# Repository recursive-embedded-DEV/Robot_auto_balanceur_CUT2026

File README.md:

# Robot_auto_balanceur_CUT2026
Ce répertoire présente les différentes étapes de conception matérielle et logicielle d'un robot auto-balanceur à deux roues créé dans le cadre d'un projet étudiant en 2026 à l'École de Technologie Supérieure (ÉTS).

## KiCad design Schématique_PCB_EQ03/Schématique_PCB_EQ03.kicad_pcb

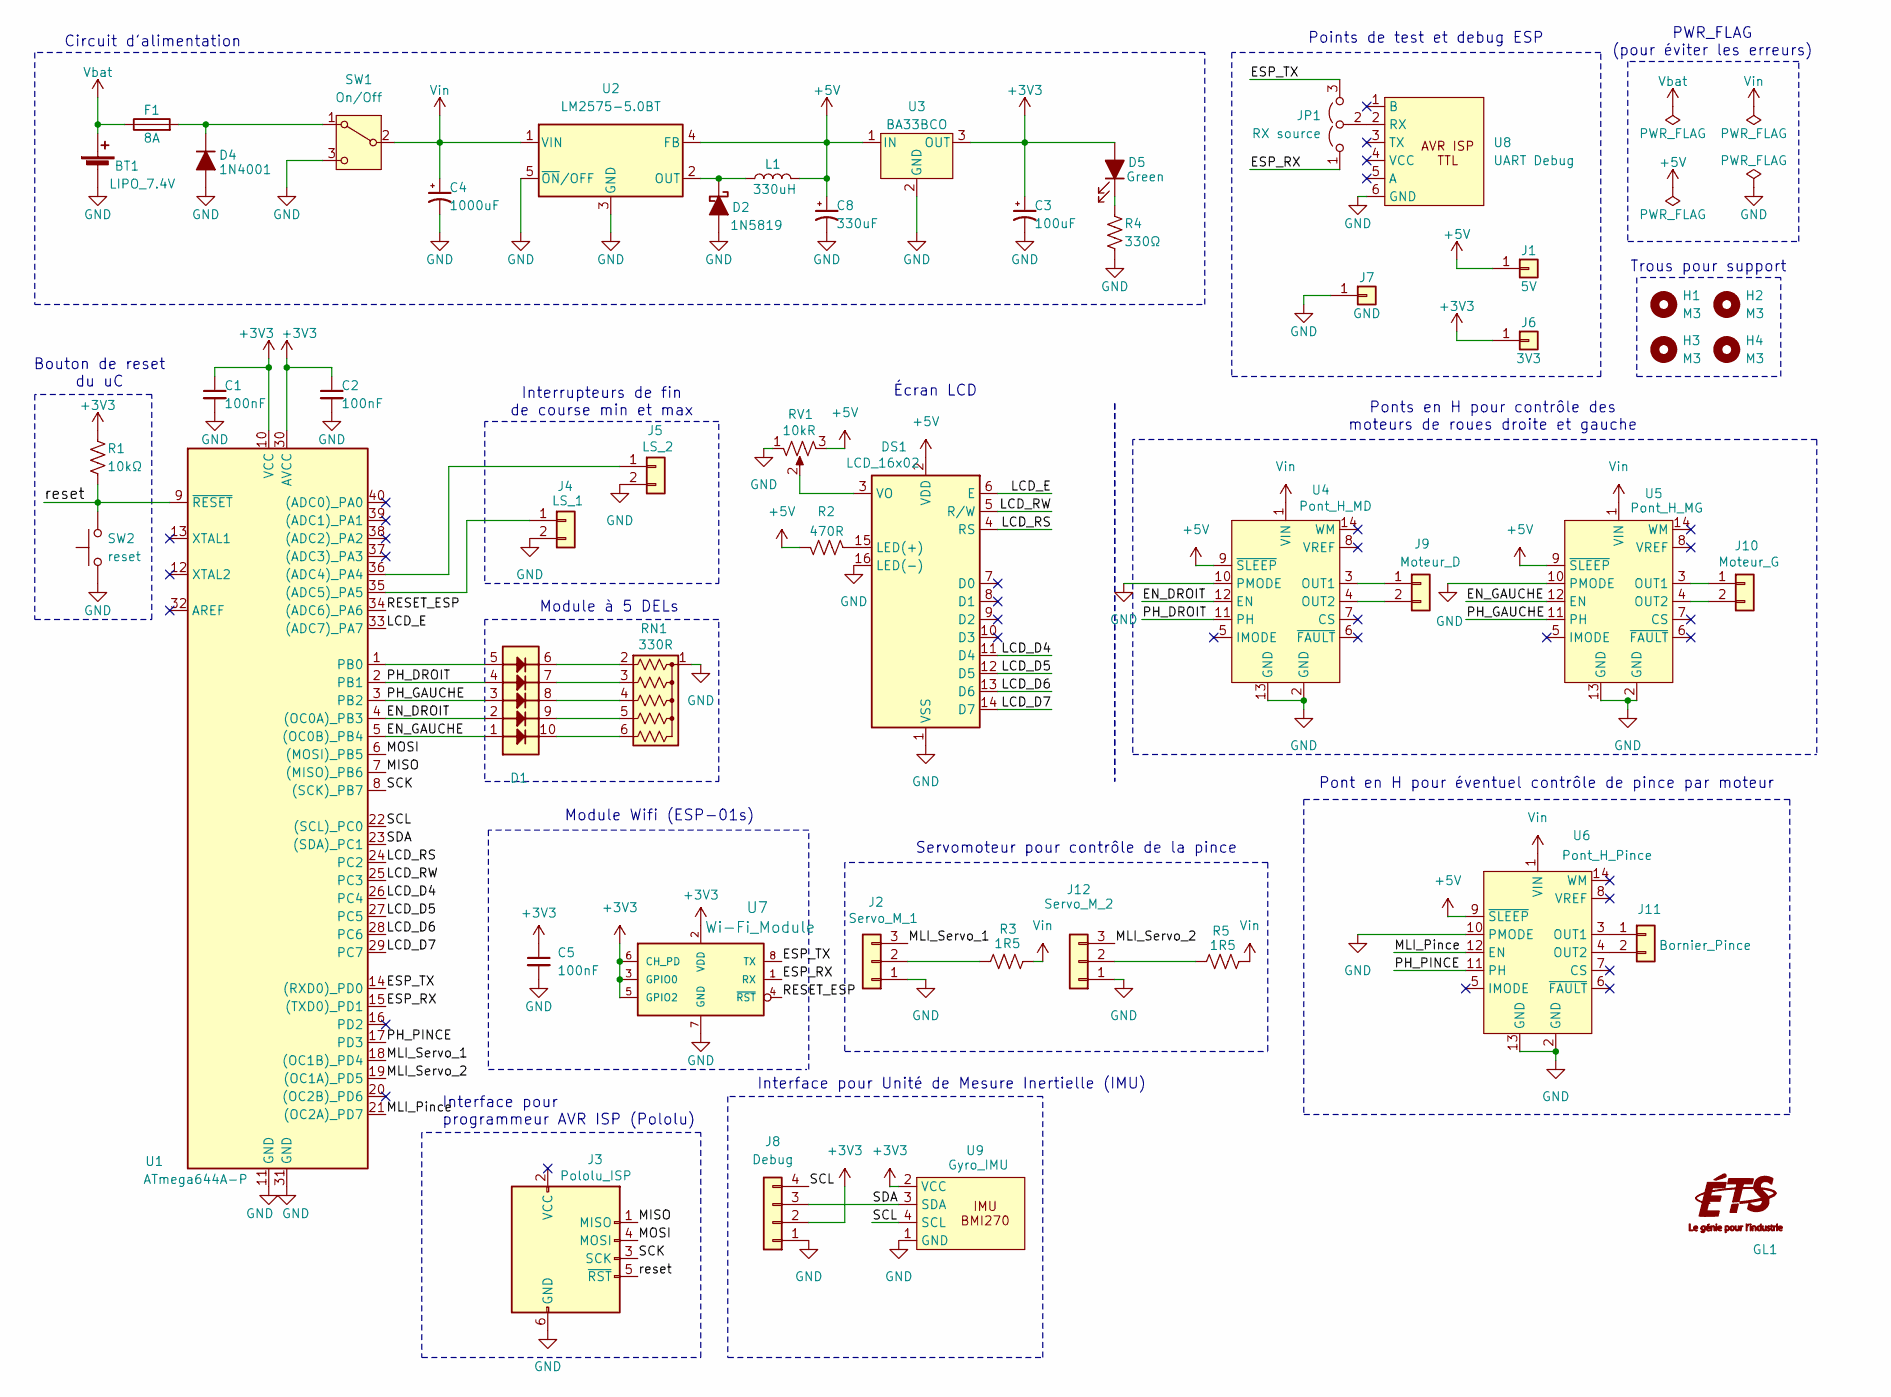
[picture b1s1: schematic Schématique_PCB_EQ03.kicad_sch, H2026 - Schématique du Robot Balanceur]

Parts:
BT1: LIPO_7.4V; Battery connector (JST RCY)
C1, C2, C5: 100nF; C_Disc_D3.4mm_W2.1mm_P2.50mm
C3: 100uF; CP_Radial_D8.0mm_P2.50mm
C4: 1000uF; CP_Radial_D13.0mm_P5.00mm
C8: 330uF; CP_Radial_D10.0mm_P5.00mm
D1: Bargraph 5 LED (XGxxX5D)
D2: 1N5819; D_DO-41_SOD81_P7.62mm_Horizontal
D4: 1N4001; D_DO-41_SOD81_P7.62mm_Horizontal
D5: Green; LED_D5.0mm
DS1: LCD_16x02; PinHeader_1x16_P2.54mm_Vertical
F1: 8A; Fuse holder (4628)
GL1: Logo ÉTS
H1, H2, H3, H4: M3; MountingHole_3.2mm_M3
J1: 5V; PinHeader_1x01_P2.54mm_Vertical
J2: Servo_M_1; Servo connector (pin header)
J3: Pololu_ISP; IDC-Header_2x03_P2.54mm_Vertical
J4: LS_1; PinHeader_1x02_P2.54mm_Vertical
J5: LS_2; PinHeader_1x02_P2.54mm_Vertical
J6: 3V3; PinHeader_1x01_P2.54mm_Vertical
J7: GND; PinHeader_1x01_P2.54mm_Vertical
J8: Debug; Qwiic connector (pin header)
J9: Moteur_D; Motor Screw Terminal (OSTTC)
J10: Moteur_G; Motor Screw Terminal (OSTTC)
J11: Bornier_Pince; Motor Screw Terminal (OSTTC)
J12: Servo_M_2; Servo connector (pin header)
JP1: RX source; PinHeader_1x03_P2.54mm_Vertical
L1: 330uH; L_Radial_D13.5mm_P7.00mm_Fastron_09HCP
R1: 10kΩ; R_Axial_DIN0207_L6.3mm_D2.5mm_P7.62mm_Horizontal
R2: 470R; R_Axial_DIN0207_L6.3mm_D2.5mm_P7.62mm_Horizontal
R3, R5: 1R5; R_Axial_DIN0309_L9.0mm_D3.2mm_P12.70mm_Horizontal
R4: 330Ω; R_Axial_DIN0207_L6.3mm_D2.5mm_P7.62mm_Horizontal
RN1: 330R; R_Array_SIP6
RV1: 10kR; Potentiometer_Bourns_3296W_Vertical
SW1: On/Off; Toggle switch SPDT (ANT11SF1CQE)
SW2: reset; SW_PUSH_6mm
U1: ATmega644A-P; Microcontroller (Atmega644A)
U2: LM2575-5.0BT; Breadboard friendly TO-220-5 (LM2575)
U3: BA33BCO; TO-220F-3_Vertical
U4: Pont_H_MD; H-bridge breakout (DRV8874)
U5: Pont_H_MG; H-bridge breakout (DRV8874)
U6: Pont_H_Pince; H-bridge breakout (DRV8874)
U7: Wi-Fi_Module; Wifi module (ESP-01S)
U8: UART Debug; TTL Debug connector (Pololu AVR)
U9: Gyro_IMU; Qwiic connector (SM04B-SRSS-TB)

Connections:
+3V3: C1.1, C2.1, C3.1, C5.1, D5.2 (A), J6.1, J8.2, R1.1, U1.10 (VCC), U1.30 (AVCC), U3.3 (OUT), U7.2 (VDD), U7.3 (GPIO0), U7.5 (GPIO2), U7.6 (CH_PD), U9.2 (VCC)
+5V: C8.1, DS1.2 (VDD), J1.1, L1.2, R2.1, RV1.3, U2.4 (FB), U3.1 (IN), U4.9 (~SLEEP), U5.9 (~SLEEP), U6.9 (~SLEEP)
/EN_DROIT: D1.2 (A2), U1.4 ((OC0A)_PB3), U4.12 (EN)
/EN_GAUCHE: D1.1 (A1), U1.5 ((OC0B)_PB4), U5.12 (EN)
/ESP_RX: JP1.1 (A), U1.15 ((TXD0)_PD1), U7.1 (RX)
/ESP_TX: JP1.3 (B), U1.14 ((RXD0)_PD0), U7.8 (TX)
/LCD_D4: DS1.11 (D4), U1.26 (PC4)
/LCD_D5: DS1.12 (D5), U1.27 (PC5)
/LCD_D6: DS1.13 (D6), U1.28 (PC6)
/LCD_D7: DS1.14 (D7), U1.29 (PC7)
/LCD_E: DS1.6 (E), U1.33 ((ADC7)_PA7)
/LCD_RS: DS1.4 (RS), U1.24 (PC2)
/LCD_RW: DS1.5 (R/W), U1.25 (PC3)
/MISO: J3.1 (MISO), U1.7 ((MISO)_PB6)
/MLI_Pince: U1.21 ((OC2A)_PD7), U6.12 (EN)
/MLI_Servo_1: J2.3, U1.18 ((OC1B)_PD4)
/MLI_Servo_2: J12.3, U1.19 ((OC1A)_PD5)
/MOSI: J3.4 (MOSI), U1.6 ((MOSI)_PB5)
/PH_DROIT: D1.4 (A4), U1.2 (PB1), U4.11 (PH)
/PH_GAUCHE: D1.3 (A3), U1.3 (PB2), U5.11 (PH)
/PH_PINCE: U1.17 (PD3), U6.11 (PH)
/RESET_ESP: U1.34 ((ADC6)_PA6), U7.4 (~RST)
/SCK: J3.3 (SCK), U1.8 ((SCK)_PB7)
/SCL: J8.4, U1.22 ((SCL)_PC0), U9.4 (SCL)
/SDA: J8.3, U1.23 ((SDA)_PC1), U9.3 (SDA)
/reset: J3.5 (~RST), R1.2, SW2.2, U1.9 (~RESET)
GND: BT1.2 (-), C1.2, C2.2, C3.2, C4.2, C5.2, C8.2, D2.2 (A), D4.2 (A), DS1.1 (VSS), DS1.16 (LED(-)), J2.1, J3.6 (GND), J4.2, J5.2, J7.1, J8.1, J12.1, R4.2, RN1.1 (common), RV1.1, SW1.3 (C), SW2.1, U1.11 (GND), U1.31 (GND), U2.3 (GND), U2.5 (~ON/OFF), U3.2 (GND), U4.2 (GND), U4.10 (PMODE), U4.13 (GND), U5.2 (GND), U5.10 (PMODE), U5.13 (GND), U6.2 (GND), U6.10 (PMODE), U6.13 (GND), U7.7 (GND), U8.6 (GND), U9.1 (GND)
unnamed: D1.5 (A5), U1.1 (PB0)
unnamed: D1.10 (K1), RN1.6 (R5)
unnamed: D1.9 (K2), RN1.5 (R4)
unnamed: D1.8 (K3), RN1.4 (R3)
unnamed: D1.7 (K4), RN1.3 (R2)
unnamed: D1.6 (K5), RN1.2 (R1)
unnamed: D2.1 (K), L1.1, U2.2 (OUT)
unnamed: D4.1 (K), F1.2, SW1.1 (A)
unnamed: D5.1 (K), R4.1
unnamed: DS1.15 (LED(+)), R2.2
unnamed: DS1.3 (VO), RV1.2
unnamed: J2.2, R3.1
unnamed: J4.1, U1.35 ((ADC5)_PA5)
unnamed: J5.1, U1.36 ((ADC4)_PA4)
unnamed: J9.1, U4.3 (OUT1)
unnamed: J9.2, U4.4 (OUT2)
unnamed: J10.1, U5.3 (OUT1)
unnamed: J10.2, U5.4 (OUT2)
unnamed: J11.1, U6.3 (OUT1)
unnamed: J11.2, U6.4 (OUT2)
unnamed: J12.2, R5.2
unnamed: JP1.2 (C), U8.2 (RX)
Vbat: BT1.1 (+), F1.1
Vin: C4.1, R3.2, R5.1, SW1.2 (B), U2.1 (VIN), U4.1 (VIN), U5.1 (VIN), U6.1 (VIN)

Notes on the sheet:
Écran LCD
Trous pour support
Pont en H pour éventuel contrôle de pince par moteur
PWR_FLAG (pour éviter les erreurs)
Circuit d'alimentation
Interface pour Unité de Mesure Inertielle (IMU)
Interrupteurs de fin de course min et max
Servomoteur pour contrôle de la pince
Module à 5 DELs
Ponts en H pour contrôle des moteurs de roues droite et gauche
Interface pour programmeur AVR ISP (Pololu)
Module Wifi (ESP-01s)
Bouton de reset du uC
Points de test et debug ESP

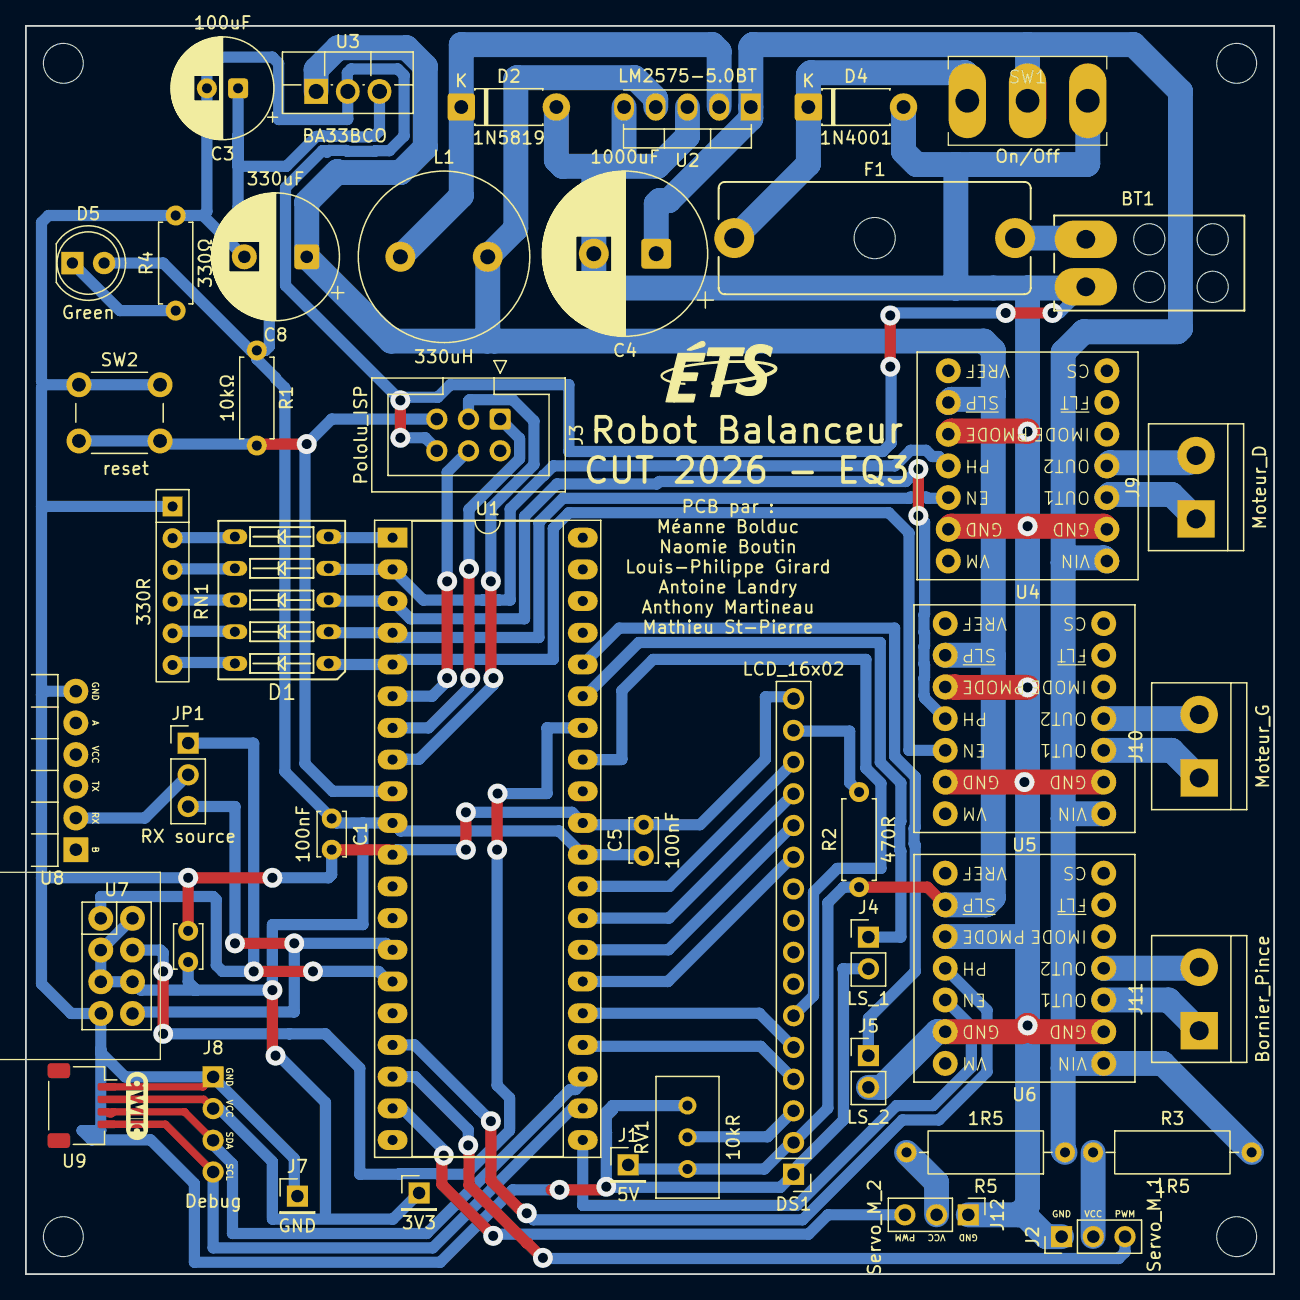
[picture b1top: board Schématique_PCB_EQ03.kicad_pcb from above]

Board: 2 copper layers, 100.0 x 100.0 mm, 50 parts (0 on the bottom side), 51 nets.

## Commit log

2026-04-26 Update README.md
    Correction d'erreurs de syntaxe.
2026-05-26 Ajout de ASSEMBLAGE_FINAL_SOLIDWORKS.zip
